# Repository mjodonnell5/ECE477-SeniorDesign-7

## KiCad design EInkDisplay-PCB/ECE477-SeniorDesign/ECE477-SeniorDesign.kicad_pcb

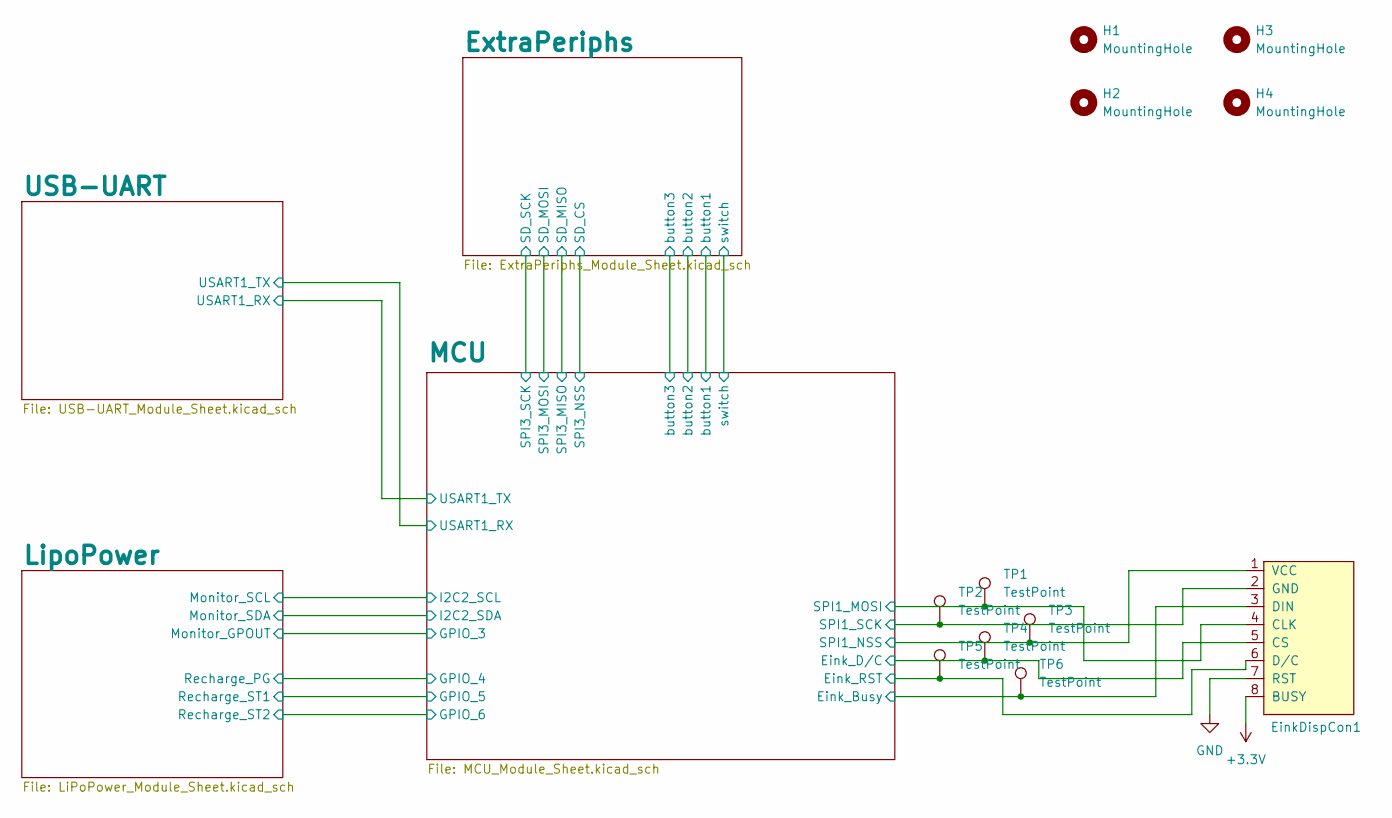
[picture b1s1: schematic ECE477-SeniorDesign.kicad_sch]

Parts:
EinkDispCon1: PinHeader_1x08_P2.54mm_Vertical
H1, H2, H3, H4: MountingHole; MountingHole_2.1mm
TP1, TP2, TP3, TP4, TP5, TP6: TestPoint; TestPoint_Pad_D2.0mm

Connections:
+3.3V: EinkDispCon1.8 (BUSY); also elsewhere on the board
/MCU/Eink_Busy: EinkDispCon1.3 (DIN), TP6.1; also elsewhere on the board
/MCU/Eink_D/C: EinkDispCon1.5 (CS), TP4.1; also elsewhere on the board
/MCU/Eink_RST: EinkDispCon1.6 (D/C), TP5.1; also elsewhere on the board
/MCU/SPI1_MOSI: EinkDispCon1.4 (CLK), TP1.1; also elsewhere on the board
/MCU/SPI1_NSS: EinkDispCon1.1 (VCC), TP3.1; also elsewhere on the board
/MCU/SPI1_SCK: EinkDispCon1.2 (GND), TP2.1; also elsewhere on the board
GND: EinkDispCon1.7 (RST); also elsewhere on the board

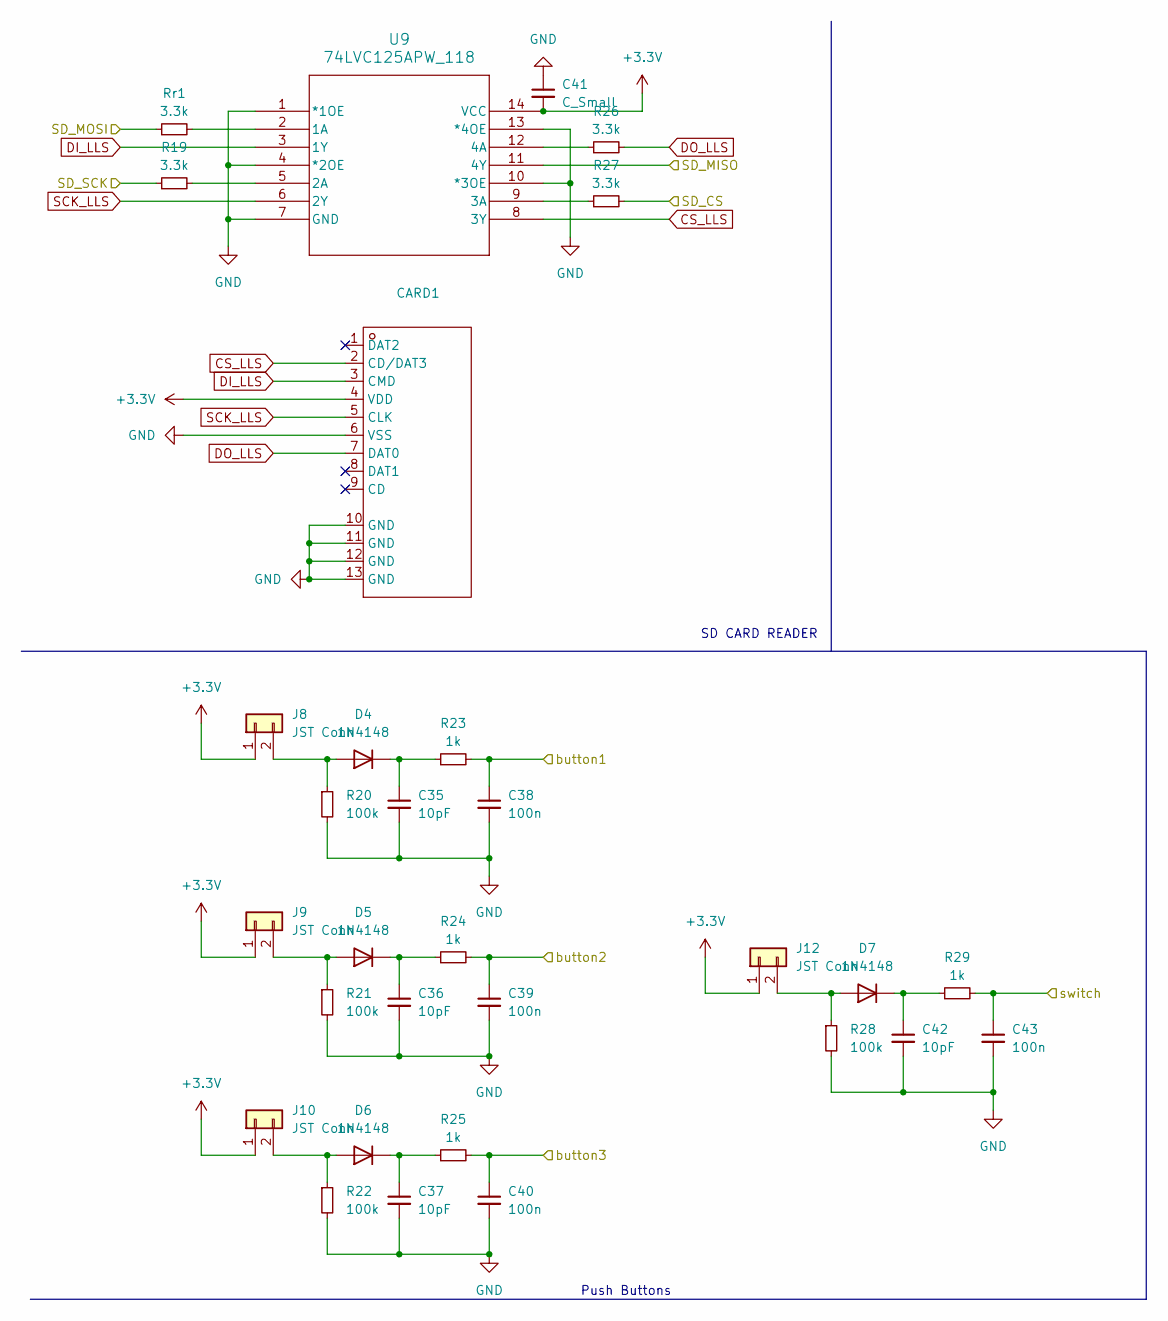
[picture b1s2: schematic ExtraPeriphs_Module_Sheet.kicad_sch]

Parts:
C35, C36, C37, C42: 10pF; C_0805_2012Metric_Pad1.18x1.45mm_HandSolder
C38, C39, C40, C43: 100n; C_0805_2012Metric_Pad1.18x1.45mm_HandSolder
C41: C_Small; C_0805_2012Metric_Pad1.18x1.45mm_HandSolder
CARD1: SD_reader_comp; Manufacturer Part XKTF-015-N; LCSC Part Name 自弹式 MicroSD卡(TF卡) 卡座
D4, D5, D6, D7: 1N4148; D_DO-35_SOD27_P7.62mm_Horizontal
J8, J9, J10, J12: JST Conn
R19, R26, R27: 3.3k; R_0805_2012Metric_Pad1.20x1.40mm_HandSolder
R20, R21, R22, R28: 100k; R_0805_2012Metric_Pad1.20x1.40mm_HandSolder
R23, R24, R25, R29: 1k; R_0805_2012Metric_Pad1.20x1.40mm_HandSolder
Rr1: 3.3k; R_0805_2012Metric_Pad1.20x1.40mm_HandSolder
U9: 74LVC125APW_118; 74LVC

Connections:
+3.3V: C41.2, CARD1.4 (VDD), J8.1, J9.1, J10.1, J12.1, U9.14 (VCC); also elsewhere on the board
/ExtraPeriphs/SD_CS: R27.2; also elsewhere on the board
/ExtraPeriphs/SD_MISO: U9.11 (4Y); also elsewhere on the board
/ExtraPeriphs/SD_MOSI: Rr1.1; also elsewhere on the board
/ExtraPeriphs/SD_SCK: R19.1; also elsewhere on the board
/ExtraPeriphs/button1: C38.1, R23.2; also elsewhere on the board
/ExtraPeriphs/button2: C39.1, R24.2; also elsewhere on the board
/ExtraPeriphs/button3: C40.1, R25.2; also elsewhere on the board
/ExtraPeriphs/switch: C43.1, R29.2; also elsewhere on the board
CS_LLS: CARD1.2 (CD/DAT3), U9.8 (3Y)
DI_LLS: CARD1.3 (CMD), U9.3 (1Y)
DO_LLS: CARD1.7 (DAT0), R26.2
GND: C35.2, C36.2, C37.2, C38.2, C39.2, C40.2, C41.1, C42.2, C43.2, CARD1.6 (VSS), CARD1.10 (GND), CARD1.11 (GND), CARD1.12 (GND), CARD1.13 (GND), R20.2, R21.2, R22.2, R28.2, U9.1 (*1OE), U9.4 (*2OE), U9.7 (GND), U9.10 (*3OE), U9.13 (*4OE); also elsewhere on the board
unnamed 44: D4.2 (A), J8.2, R20.1; also elsewhere on the board
unnamed: C35.1, D4.1 (K), R23.1
unnamed: D5.2 (A), J9.2, R21.1
unnamed: C36.1, D5.1 (K), R24.1
unnamed: D6.2 (A), J10.2, R22.1
unnamed: C37.1, D6.1 (K), R25.1
unnamed: D7.2 (A), J12.2, R28.1
unnamed: C42.1, D7.1 (K), R29.1
unnamed: Rr1.2, U9.2 (1A)
unnamed: R19.2, U9.5 (2A)
unnamed: R27.1, U9.9 (3A)
unnamed: R26.1, U9.12 (4A)
SCK_LLS: CARD1.5 (CLK), U9.6 (2Y)

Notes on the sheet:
SD CARD READER
Push Buttons

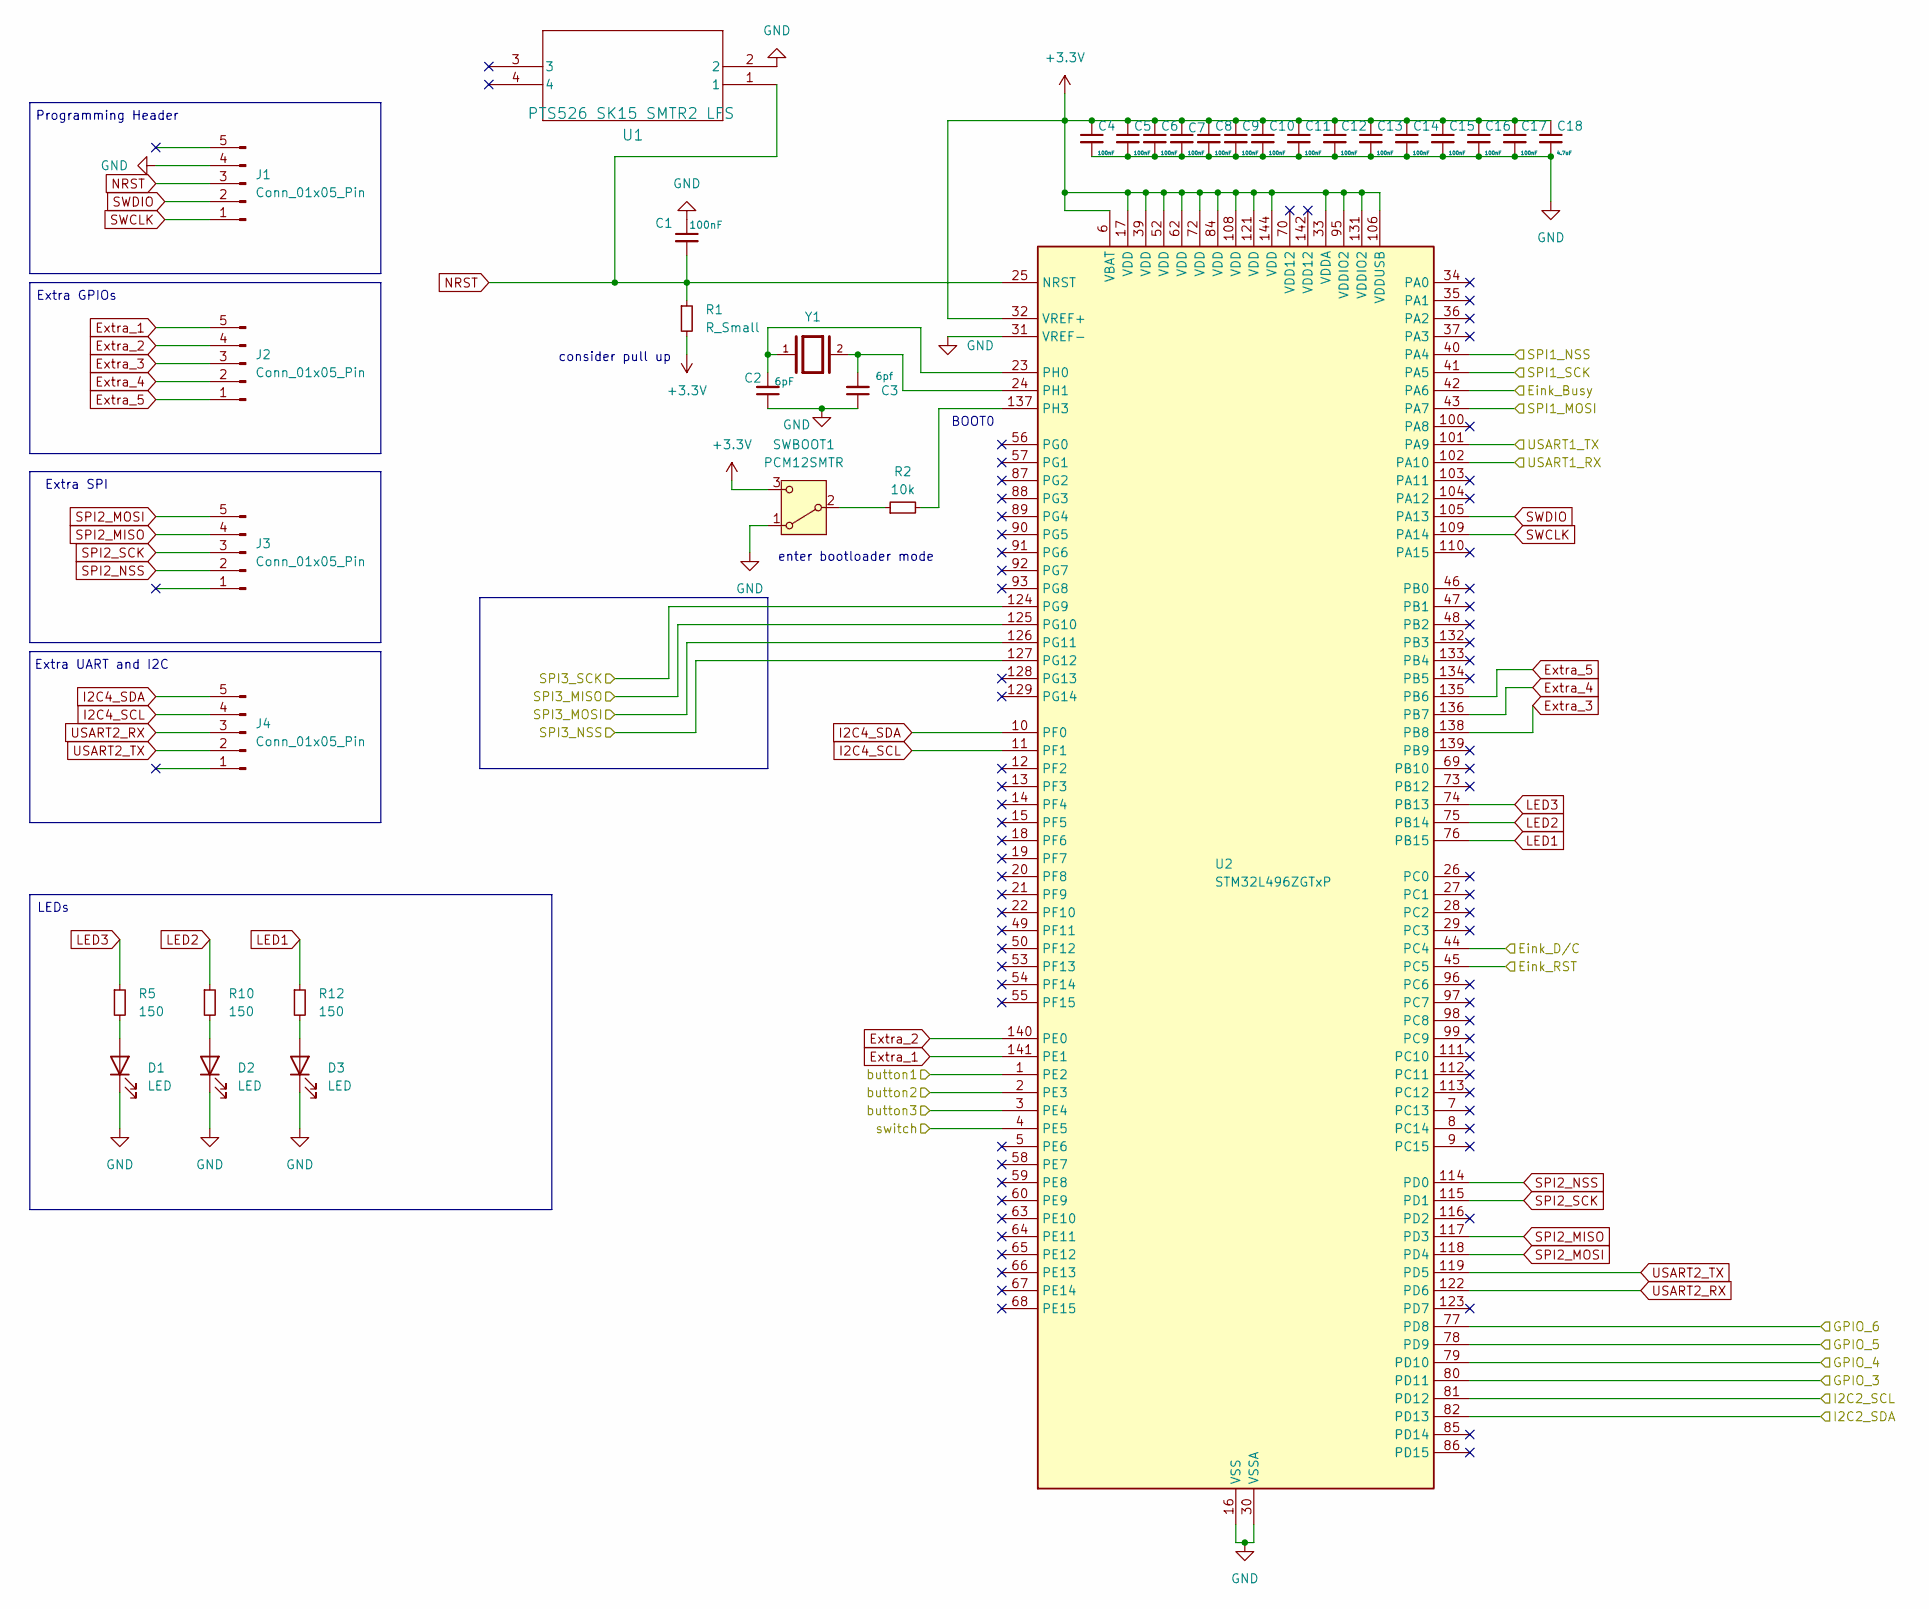
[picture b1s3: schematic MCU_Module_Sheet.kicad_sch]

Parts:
C1, C4, C5, C6, C7, C8, C9, C10, C11, C12, C13, C14, C15, C16, C17: 100nF; C_0805_2012Metric_Pad1.18x1.45mm_HandSolder
C2: 6pF; C_0805_2012Metric_Pad1.18x1.45mm_HandSolder
C3: 6pf; C_0805_2012Metric_Pad1.18x1.45mm_HandSolder
C18: 4.7uF; C_0805_2012Metric_Pad1.18x1.45mm_HandSolder
D1, D2, D3: LED; LED_0603_1608Metric
J1, J2, J3, J4: Conn_01x05_Pin; PinHeader_1x05_P2.54mm_Vertical
R1: R_Small; R_0805_2012Metric_Pad1.20x1.40mm_HandSolder
R2: 10k; R_0603_1608Metric_Pad0.98x0.95mm_HandSolder
R5, R10, R12: 150; R_0805_2012Metric_Pad1.20x1.40mm_HandSolder
SWBOOT1: PCM12SMTR; SW_SPDT_PCM12
U1: PTS526 SK15 SMTR2 LFS; PTS256
U2: STM32L496ZGTxP; LQFP-144_20x20mm_P0.5mm
Y1: CM9V-T1A-32.768KHZ-7PF-100PPM-TA-QC; PARTREV 8.0/10.2016

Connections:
+3.3V: C4.1, C5.1, C6.1, C7.1, C8.1, C9.1, C10.1, C11.1, C12.1, C13.1, C14.1, C15.1, C16.1, C17.1, C18.1, R1.2, SWBOOT1.3 (C), U2.6 (VBAT), U2.17 (VDD), U2.32 (VREF+), U2.33 (VDDA), U2.39 (VDD), U2.52 (VDD), U2.62 (VDD), U2.72 (VDD), U2.84 (VDD), U2.95 (VDDIO2), U2.106 (VDDUSB), U2.108 (VDD), U2.121 (VDD), U2.131 (VDDIO2), U2.144 (VDD); also elsewhere on the board
/ExtraPeriphs/SD_CS: U2.127 (PG12); also elsewhere on the board
/ExtraPeriphs/SD_MISO: U2.125 (PG10); also elsewhere on the board
/ExtraPeriphs/SD_MOSI: U2.126 (PG11); also elsewhere on the board
/ExtraPeriphs/SD_SCK: U2.124 (PG9); also elsewhere on the board
/ExtraPeriphs/button1: U2.1 (PE2); also elsewhere on the board
/ExtraPeriphs/button2: U2.2 (PE3); also elsewhere on the board
/ExtraPeriphs/button3: U2.3 (PE4); also elsewhere on the board
/ExtraPeriphs/switch: U2.4 (PE5); also elsewhere on the board
/LipoPower/Monitor_GPOUT: U2.80 (PD11); also elsewhere on the board
/LipoPower/Monitor_SCL: U2.81 (PD12); also elsewhere on the board
/LipoPower/Monitor_SDA: U2.82 (PD13); also elsewhere on the board
/LipoPower/Recharge_PG: U2.79 (PD10); also elsewhere on the board
/LipoPower/Recharge_ST1: U2.78 (PD9); also elsewhere on the board
/LipoPower/Recharge_ST2: U2.77 (PD8); also elsewhere on the board
/MCU/Eink_Busy: U2.42 (PA6); also elsewhere on the board
/MCU/Eink_D/C: U2.44 (PC4); also elsewhere on the board
/MCU/Eink_RST: U2.45 (PC5); also elsewhere on the board
/MCU/SPI1_MOSI: U2.43 (PA7); also elsewhere on the board
/MCU/SPI1_NSS: U2.40 (PA4); also elsewhere on the board
/MCU/SPI1_SCK: U2.41 (PA5); also elsewhere on the board
/MCU/USART1_RX: U2.102 (PA10); also elsewhere on the board
/MCU/USART1_TX: U2.101 (PA9); also elsewhere on the board
Extra_1: J2.5, U2.141 (PE1)
Extra_2: J2.4, U2.140 (PE0)
Extra_3: J2.3, U2.138 (PB8)
Extra_4: J2.2, U2.136 (PB7)
Extra_5: J2.1, U2.135 (PB6)
GND: C1.1, C2.1, C3.1, C4.2, C5.2, C6.2, C7.2, C8.2, C9.2, C10.2, C11.2, C12.2, C13.2, C14.2, C15.2, C16.2, C17.2, C18.2, D1.1 (K), D2.1 (K), D3.1 (K), J1.4, SWBOOT1.1 (A), U1.2, U2.16 (VSS), U2.30 (VSSA), U2.31 (VREF-), U2.38 (VSS), U2.51 (VSS), U2.61 (VSS), U2.71 (VSS), U2.83 (VSS), U2.94 (VSS), U2.107 (VSS), U2.120 (VSS), U2.130 (VSS), U2.143 (VSS); also elsewhere on the board
I2C4_SCL: J4.4, U2.11 (PF1)
I2C4_SDA: J4.5, U2.10 (PF0)
LED1: R12.1, U2.76 (PB15)
LED2: R10.1, U2.75 (PB14)
LED3: R5.1, U2.74 (PB13)
NRST: C1.2, J1.3, R1.1, U1.1, U2.25 (NRST)
unnamed: D1.2 (A), R5.2
unnamed: D2.2 (A), R10.2
unnamed: D3.2 (A), R12.2
unnamed: R2.1, SWBOOT1.2 (B)
unnamed: C2.2, U2.23 (PH0), Y1.1
unnamed: C3.2, U2.24 (PH1), Y1.2
unnamed: R2.2, U2.137 (PH3)
SPI2_MISO: J3.4, U2.117 (PD3)
SPI2_MOSI: J3.5, U2.118 (PD4)
SPI2_NSS: J3.2, U2.114 (PD0)
SPI2_SCK: J3.3, U2.115 (PD1)
SWCLK: J1.1, U2.109 (PA14)
SWDIO: J1.2, U2.105 (PA13)
USART2_RX: J4.3, U2.122 (PD6)
USART2_TX: J4.2, U2.119 (PD5)

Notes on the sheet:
consider pull up
BOOT0
Extra UART and I2C
Programming Header
enter bootloader mode
Extra SPI
Extra GPIOs
LEDs

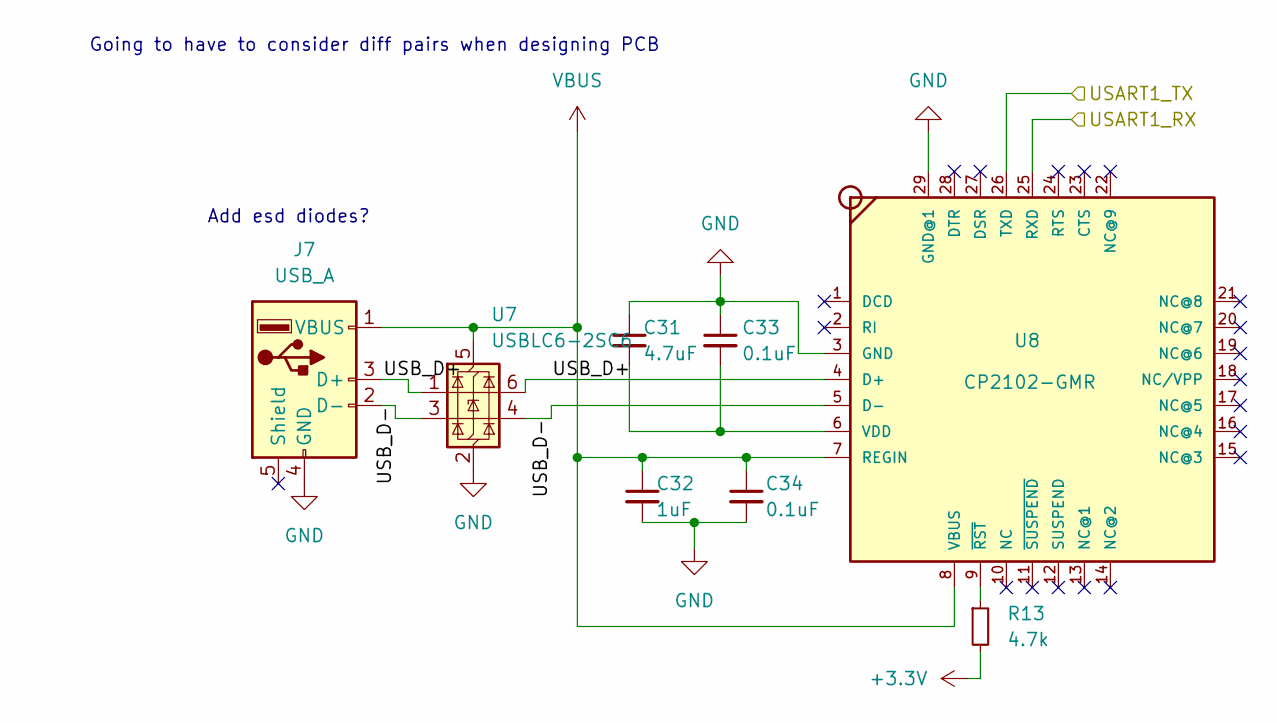
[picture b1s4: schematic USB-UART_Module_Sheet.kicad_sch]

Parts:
C31: 4.7uF; C_0805_2012Metric_Pad1.18x1.45mm_HandSolder
C32: 1uF; C_0805_2012Metric_Pad1.18x1.45mm_HandSolder
C33, C34: 0.1uF; C_0805_2012Metric_Pad1.18x1.45mm_HandSolder
J7: USB_A; USB_A_Receptacle_GCT_USB1046
R13: 4.7k; R_0805_2012Metric_Pad1.20x1.40mm_HandSolder
U7: USBLC6-2SC6; SOT-23-6
U8: CP2102-GMR; CP2102; MPN CP2102-GMR

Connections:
+3.3V: R13.2; also elsewhere on the board
/MCU/USART1_RX: U8.26 (TXD); also elsewhere on the board
/MCU/USART1_TX: U8.25 (RXD); also elsewhere on the board
/USB-UART/USB_D+: J7.3 (D+), U7.1 (I/O1), U7.6 (I/O1), U8.4 (D+)
/USB-UART/USB_D-: J7.2 (D-), U7.3 (I/O2), U7.4 (I/O2), U8.5 (D-)
GND: C31.1, C32.2, C33.1, C34.2, J7.4 (GND), J7.5 (Shield), U7.2 (GND), U8.3 (GND), U8.29 (GND@1); also elsewhere on the board
unnamed: C31.2, C33.2, U8.6 (VDD)
unnamed: R13.1, U8.9 (~RST)
VBUS: C32.1, C34.1, J7.1 (VBUS), U7.5 (VBUS), U8.7 (REGIN), U8.8 (VBUS); also elsewhere on the board

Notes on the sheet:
Add esd diodes?
Going to have to consider diff pairs when designing PCB

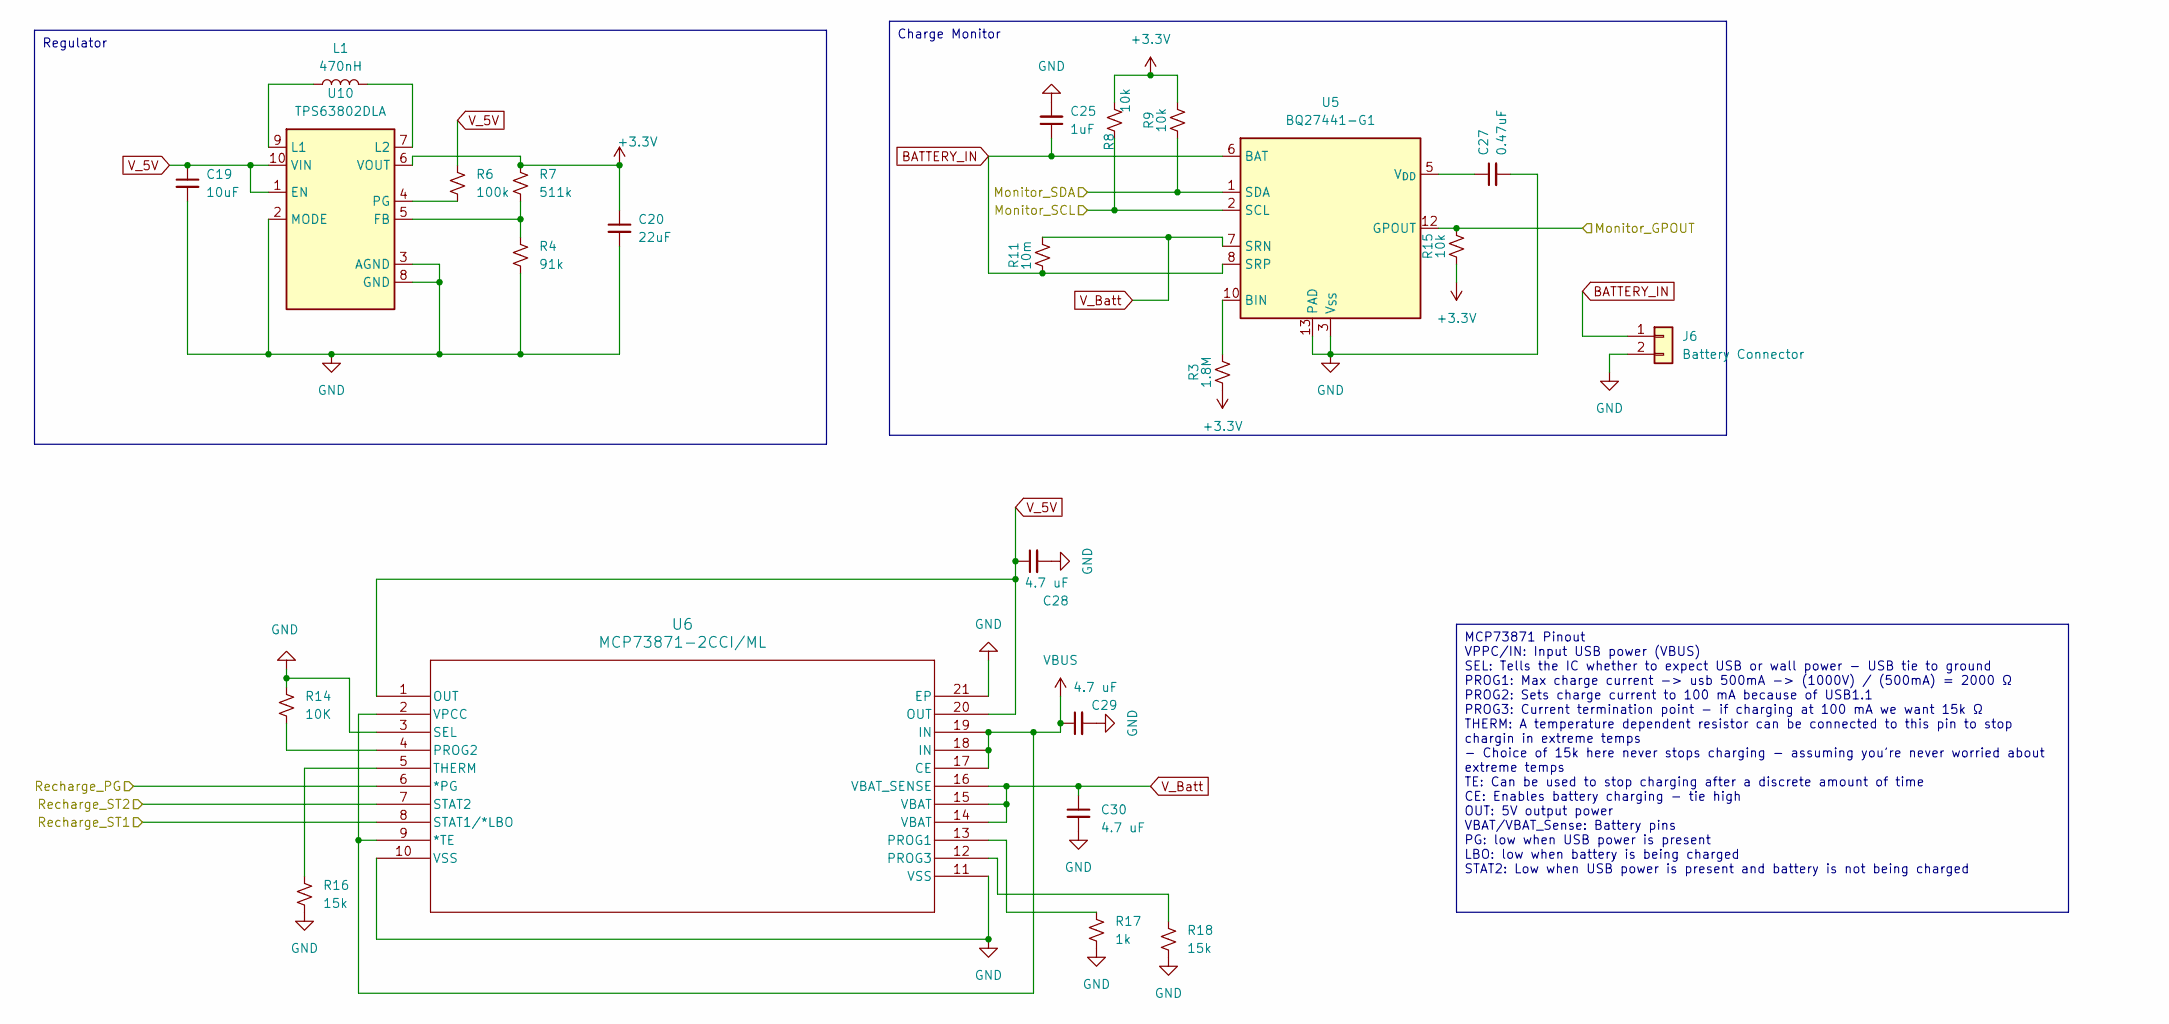
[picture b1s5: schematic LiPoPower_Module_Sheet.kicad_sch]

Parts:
C19: 10uF; C_0805_2012Metric_Pad1.18x1.45mm_HandSolder
C20: 22uF; C_0805_2012Metric_Pad1.18x1.45mm_HandSolder
C25: 1uF; C_0805_2012Metric_Pad1.18x1.45mm_HandSolder
C27: 0.47uF; C_0805_2012Metric_Pad1.18x1.45mm_HandSolder
C28, C29, C30: 4.7 uF; C_0805_2012Metric_Pad1.18x1.45mm_HandSolder
J6: Battery Connector; JST_PH_S2B-PH-SM4-TB_1x02-1MP_P2.00mm_Horizontal
L1: 470nH; IND_XFL4015_COC-L
R3: 1.8M; R_0805_2012Metric_Pad1.20x1.40mm_HandSolder
R4: 91k; R_0805_2012Metric_Pad1.20x1.40mm_HandSolder
R6: 100k; R_0805_2012Metric_Pad1.20x1.40mm_HandSolder
R7: 511k; R_0805_2012Metric_Pad1.20x1.40mm_HandSolder
R8, R9, R15: 10k; R_0805_2012Metric_Pad1.20x1.40mm_HandSolder
R11: 10m; R_0805_2012Metric_Pad1.20x1.40mm_HandSolder
R14: 10K; R_0805_2012Metric_Pad1.20x1.40mm_HandSolder
R16, R18: 15k; R_0805_2012Metric_Pad1.20x1.40mm_HandSolder
R17: 1k; R_0805_2012Metric_Pad1.20x1.40mm_HandSolder
U5: BQ27441-G1; Texas_S-PDSO-N12
U6: MCP73871-2CCI/ML; MCP73871; LCSC C5121473
U10: TPS63802DLA; TPS63802DLR; LCSC C2845237

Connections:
+3.3V: C20.1, R3.1, R7.1, R8.2, R9.2, R15.1, U10.6 (VOUT); also elsewhere on the board
/LipoPower/Monitor_GPOUT: R15.2, U5.12 (GPOUT); also elsewhere on the board
/LipoPower/Monitor_SCL: R8.1, U5.2 (SCL); also elsewhere on the board
/LipoPower/Monitor_SDA: R9.1, U5.1 (SDA); also elsewhere on the board
/LipoPower/Recharge_PG: U6.6 (*PG); also elsewhere on the board
/LipoPower/Recharge_ST1: U6.8 (STAT1/*LBO); also elsewhere on the board
/LipoPower/Recharge_ST2: U6.7 (STAT2); also elsewhere on the board
BATTERY_IN: C25.1, J6.1, R11.1, U5.6 (BAT), U5.8 (SRP)
GND: C19.2, C20.2, C25.2, C27.2, C28.2, C29.2, C30.2, J6.2, R4.2, R14.1, R16.1, R17.2, R18.1, U5.3 (V_{SS}), U5.13 (PAD), U6.3 (SEL), U6.10 (VSS), U6.11 (VSS), U6.21 (EP), U10.2 (MODE), U10.3 (AGND), U10.8 (GND); also elsewhere on the board
unnamed: R3.2, U5.10 (BIN)
unnamed: C27.1, U5.5 (V_{DD})
unnamed: R17.1, U6.13 (PROG1)
unnamed: R14.2, U6.4 (PROG2)
unnamed: R18.2, U6.12 (PROG3)
unnamed: R16.2, U6.5 (THERM)
unnamed: R4.1, R7.2, U10.5 (FB)
unnamed: L1.1, U10.9 (L1)
unnamed: L1.2, U10.7 (L2)
unnamed: R6.1, U10.4 (PG)
VBUS: C29.1, U6.2 (VPCC), U6.9 (*TE), U6.17 (CE), U6.18 (IN), U6.19 (IN); also elsewhere on the board
V_5V: C19.1, C28.1, R6.2, U6.1 (OUT), U6.20 (OUT), U10.1 (EN), U10.10 (VIN)
V_Batt: C30.1, R11.2, U5.7 (SRN), U6.14 (VBAT), U6.15 (VBAT), U6.16 (VBAT_SENSE)

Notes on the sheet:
Charge Monitor
MCP73871 Pinout VPPC/IN: Input USB power (VBUS) SEL: Tells the IC whether to expect USB or wall power - USB tie to ground PROG1: Max charge current -> usb 500mA -> (1000V) / (500mA) = 2000 Ω PROG2: Sets charge current to 100 mA because of USB1.1 PROG3: Current termination point - if charging at 100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
Regulator

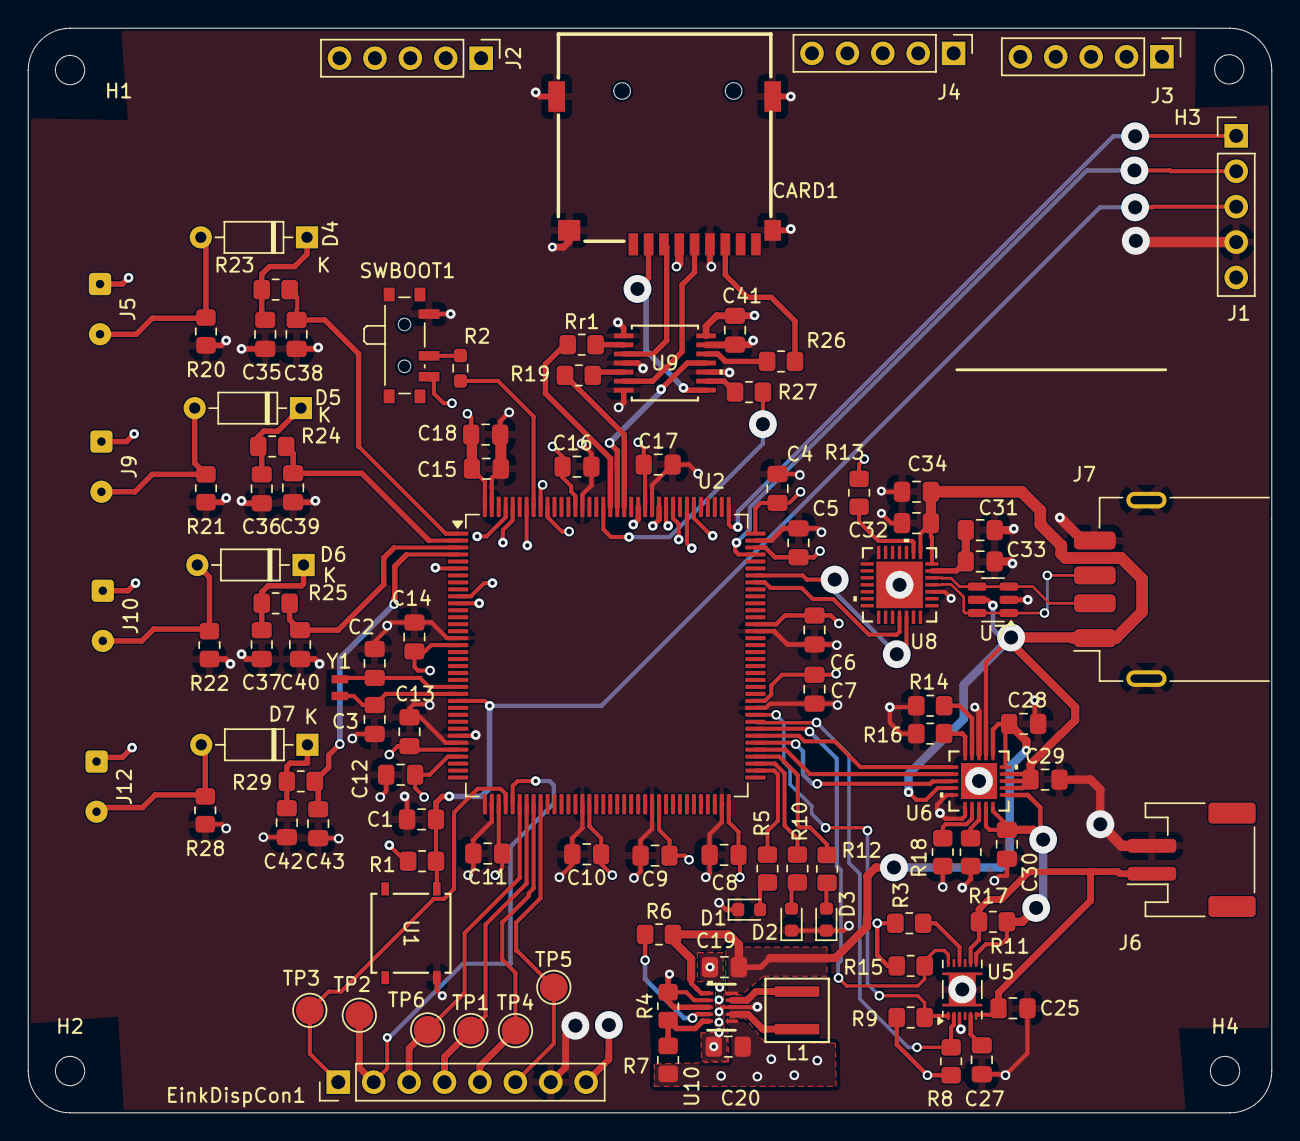
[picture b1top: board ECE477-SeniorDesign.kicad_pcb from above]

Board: 4 copper layers, 89.2 x 77.8 mm, 108 parts (0 on the bottom side), 84 nets.

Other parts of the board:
J5: Conn_01x02; SolderWire-0.1sqmm_1x02_P3.6mm_D0.4mm_OD1mm

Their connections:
+3.3V: J5.1; also elsewhere on the board
unnamed 44: J5.2; also elsewhere on the board

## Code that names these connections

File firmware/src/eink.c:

#include <stdint.h>
#include <stddef.h>
#include <string.h>
#include <stm32l496xx.h>

#include "../include/spi.h"
#include "../include/eink.h"
#include "../include/clock.h"
#include "../include/state.h"

uint8_t framebuffer[EINK_FRAMEBUFFER_SIZE] = {0xFF};
volatile uint8_t eink_busy = 0;

static void eink_send_cmd(uint8_t cmd)
{
    /* D/C low */
    GPIOC->BSRR = GPIO_BSRR_BR4;

    /* CS low */
    GPIOA->BSRR = GPIO_BSRR_BR4;

    spi_tx(EINK_SPI, cmd);

    /* CS high */
    GPIOA->BSRR = GPIO_BSRR_BS4;
}

static void eink_send_data(uint8_t data)
{
    /* D/C high */
    GPIOC->BSRR = GPIO_BSRR_BS4;

    /* CS low */
    GPIOA->BSRR = GPIO_BSRR_BR4;

    spi_tx(EINK_SPI, data);

    /* CS high */
    GPIOA->BSRR = GPIO_BSRR_BS4;
}

static void eink_pin_init()
{
    RCC->AHB2ENR |= RCC_AHB2ENR_GPIOAEN; //turn on A
    RCC->AHB2ENR |= RCC_AHB2ENR_GPIOCEN; //turn on C

    /* BUSY - PA6 (INPUT) ; RESET - PA9 ; D/C - PA8 */
    GPIOA->MODER &= ~(GPIO_MODER_MODER6 );
    RCC->APB2ENR |= RCC_APB2ENR_SYSCFGEN;
    SYSCFG->EXTICR[1] |= SYSCFG_EXTICR2_EXTI6_PA;
    EXTI->FTSR1 |= EXTI_FTSR1_FT6;
    EXTI->IMR1 |= EXTI_IMR1_IM6;

    NVIC->ISER[0] |= (1 << EXTI9_5_IRQn);
    // GPIOA->MODER |= (GPIO_MODER_MODER8_0 | GPIO_MODER_MODER9_0);

    /*; RESET - PC5 ; D/C - PC4 */
    GPIOC->MODER &= ~(GPIO_MODER_MODER4 | GPIO_MODER_MODER5);
    GPIOC->MODER |= (GPIO_MODER_MODER4_0 | GPIO_MODER_MODER5_0);

    /* High speed ...might need these?*/
    // GPIOA->OSPEEDR &= ~(GPIO_OSPEEDR_OSPEED6 | GPIO_OSPEEDR_OSPEED8 | GPIO_OSPEEDR_OSPEED9);
    // GPIOA->OSPEEDR |= GPIO_OSPEEDR_OSPEED6_1 | GPIO_OSPEEDR_OSPEED8_1 | GPIO_OSPEEDR_OSPEED9_1;

}


void eink_wait_until_idle()
{
    /* The all mightly magical command */
    // eink_send_cmd(0x71);

    // while((GPIOA->IDR & GPIO_IDR_ID6) == 1) {
    //     eink_send_cmd(0x71);
    // }
    while (eink_busy == 1) {};

    // delay_ms(100);
}

static void eink_reset()
{
    /* Set RESET high */
    GPIOC->BSRR = GPIO_BSRR_BS5;
    delay_ms(100);

    /* RESET is active low */
    GPIOC->BSRR = GPIO_BSRR_BR5;

    delay_ms(2);

    /* Set RESET high */
    GPIOC->BSRR = GPIO_BSRR_BS5;

    delay_ms(100);
}

void eink_init()
{
    eink_pin_init();

    eink_reset();
    eink_send_cmd(0x12);
    eink_wait_until_idle();
    delay_ms(100);

    delay_ms(10);

    eink_send_cmd(0x21);
    eink_send_data(0x40);
    eink_send_data(0x00);

    eink_send_cmd(0x3C);
    eink_send_data(0x05);

    /* Stuff for FAST MODE */
    eink_send_cmd(0x1A);
    eink_send_data(0x5A);
    eink_send_cmd(0x22);
    eink_send_data(0x91);
    eink_send_cmd(0x20);
    eink_wait_until_idle();
    delay_ms(100);

    eink_send_cmd(0x11);
    if (left_handed) {
        eink_send_data(0x03);
    } else {
        eink_send_data(0x00);
    }

    eink_send_cmd(0x44); 
    if (left_handed) {
        eink_send_data(0x00);
        eink_send_data(0x31); 
    } else {
        eink_send_data(0x31); 
        eink_send_data(0x00);
    }
    
    eink_send_cmd(0x45);
    if (left_handed) {
        eink_send_data(0x00);
        eink_send_data(0x00);  
        eink_send_data(0x2B);
        eink_send_data(0x01);
    } else {
        eink_send_data(0x2B);
        eink_send_data(0x01);
        eink_send_data(0x00);
        eink_send_data(0x00);  
    }

    if (left_handed) {
        eink_send_cmd(0x4E); 
        eink_send_data(0x00);

        eink_send_cmd(0x4F); 
        eink_send_data(0x00);
        eink_send_data(0x00);  
    } else {
        eink_send_cmd(0x4E); 
        eink_send_data(0x31);

        eink_send_cmd(0x4F); 
        eink_send_data(0x2B);
        eink_send_data(0x01);  
    }
    eink_wait_until_idle();
    // delay_ms(100);
}

inline void eink_draw_pixel(uint16_t x, uint16_t y, uint8_t col)
{
    uint32_t index = y * EINK_WIDTH + x;
    uint16_t byte_index = index / 8;

    if (x >= EINK_WIDTH || y >= EINK_HEIGHT) return;

    if (col == WHITE) {
        framebuffer[byte_index] |= (0x80 >> (x % 8));
    } else {
        framebuffer[byte_index] &= ~(0x80 >> (x % 8));
    }
}

static void eink_turn_on_display()
{
    /* FAST MODE */
    eink_send_cmd(0x22);
    eink_send_data(0xC7);
    eink_send_cmd(0x20);
    eink_wait_until_idle();
}

void eink_render_framebuffer()
{
    eink_busy = 1;
    /* Start writing into B/W ram */
    eink_send_cmd(0x24);

    for (uint16_t i = 0; i < EINK_FRAMEBUFFER_SIZE; ++i) {
        eink_send_data(framebuffer[i]);
    }

    eink_turn_on_display();
}

void eink_clear(uint8_t col)
{
    memset(framebuffer, col, EINK_FRAMEBUFFER_SIZE);
}

void eink_sleep()
{
    eink_send_cmd(0x10);
    eink_send_data(0x01);
    delay_ms(100);
}

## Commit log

2025-01-16 Add Blocks
    Adding USB-UART block
2025-01-28 Pushing some basic SPI stuff, init is not setup for epaper at the moment and is just copied from 362
2025-01-28 I think SPI config for eink should be good
2025-01-28 Accidently pushed the default READMEs and a personal config file
2025-01-28 Starting to setup eink init based on data sheet, I will go through and see what we need to modify once I copy it all from the data sheet
2025-01-28 Edits
2025-01-28 switching over to V2
2025-01-28 Adding Power Sheet
2025-01-28 Adding Component Library
    -named einkcomponent library
2025-01-28 Trying to add some drawing functions and rendering the framebuffer
2025-01-30 USB Complete
2025-01-30 Pushing because its broken :(
2025-01-30 Lot of changes
2025-02-02 push
2025-02-03 Still scrambled
2025-02-04 Adding SD
2025-02-04 fixing
2025-02-04 It works, thanks Zoe
2025-02-04 Fixing SD w SPI
2025-02-05 Cleaning stuff up and optimizing a bit
2025-02-05 IT WORKS
2025-02-06 eink stuff should be done
2025-02-12 introducing power sch
2025-02-12 fixing things
2025-02-12 should have pushed before, also this is not based on main so hopefully no merge conflicts
2025-02-13 adding my sd card code ALLL
2025-02-14 0805
2025-02-15 Testing wrapping of strings and displaying flashcards
2025-02-15 I forget
2025-02-18 Testing adding flashcard front/backs
2025-02-18 adding skeleton functions until SD stuff is done
2025-02-19 Update USB-UART_Module_Sheet.kicad_sch
    Add ESD diode
2025-02-19 Update ECE477-SeniorDesign.kicad_pcb
    All UART / Voltage reg components
2025-02-19 change
2025-02-19 Pushing
2025-02-19 adding UART files
2025-02-19 SD_Reader Footprint
2025-02-20 Starting to clean up, I really should make a new branch though lol
2025-02-20 Lotta changes
2025-02-20 added parseJSON_file and changed main
2025-02-20 Did a decent amount of cleanup and moved buttons so Zoe and I can integrate
2025-02-21 Clock stuff, not finished
2025-02-21 Scrolling, clock, delaying, all kinds of fun stuff. This PR is WAY too big lol
2025-02-21 fixed pinout
2025-02-21 new sd card name
2025-02-21 Moving stuff to firmware
2025-02-21 RAAAAAAAAAAAAAAAAA
2025-02-22 centered!
2025-02-22 Prepping for download
2025-02-23 onto PCB
2025-02-23 SD card updates
2025-02-23 power & power pcb layout
2025-02-24 Setting up download flashcards
2025-02-25 Correcting
2025-02-25 Ensuring file save
2025-02-25 layout and coulomb counter sch update
2025-02-26 pcb update
2025-02-27 whole lotta changes
2025-02-27 We can get files over UART
2025-02-27 Layout update
2025-02-28 Fixed clock frequency, centered string wrapping and did some cleaning up
2025-02-28 Can now receive again with clock updates
2025-03-02 Added bounds checking and better headers
2025-03-03 Power Routing
2025-03-03 adding application v1 and v2
2025-03-03 finished cleanup
2025-03-03 again
2025-03-04 pusj
2025-03-04 done
2025-03-05 I implemented font stuff but am not in lab to test
2025-03-06 pusbh
2025-03-06 Variable fonts work!
2025-03-06 Regulator footprint and sch update
2025-03-07 app v3 added
2025-03-11 Sch update
2025-03-12 Setup basic stuff to get it ready
2025-03-12 changes to new app
2025-03-12 LONG PRESSING WORKS
2025-03-13 rev 2
2025-03-13 rev3
2025-03-13 new commands
2025-03-13 add set name
2025-03-13 implementing state logic in regards to the long button press
2025-03-13 I am dumb and not pending the render and I had the state machine messed up, it was running too fast, need delay or to WFI
2025-03-26 size restriction
2025-03-26 not working now?
2025-03-27 Refactor button and state machine stuff
2025-03-31 This branch is just random stuff at this point, added delete confirmation and am starting to add settings
2025-04-01 newest app
2025-04-01 adding battery code
2025-04-01 Forgot to actually implement the shuffling
2025-04-02 battery changes
2025-04-02 new pins
2025-04-02 all added - cole check
2025-04-03 Power stuff should work, just haven't set up power switch pinout stuff
2025-04-03 Starting to disable stuff
2025-04-03 centering
2025-04-04 scroll but glitchy!
2025-04-07 newest changes
2025-04-07 new pins uart
2025-04-08 Lotta UI changes
2025-04-09 fixing appv3 on this branch
2025-04-09 app has new format
2025-04-09 Forgot to push yesterday
2025-04-10 changes to the firmware side
2025-04-10 sike using a struct
2025-04-10 build error fix
2025-04-10 RTC seems to work
2025-04-10 rtc stuff and setting up sd card reader
2025-04-11 new battery pins
2025-04-13 I forget lol
2025-04-13 Readding writing to the SD when downloading
2025-04-14 tested num cards, works!
2025-04-14 adding long filenames
2025-04-17 Gotta switch back
2025-04-17 Variable fonts, can choose dominant hand, button hints
2025-04-17 good app!
2025-04-17 metadata stuff added but not tested
2025-04-17 Fixed button hints for right handed mode
2025-04-18 Eink busy works properly :)
2025-04-20 Rewrite complete, haven't tested anything except home nav yet
2025-04-20 starting to think aobut coalescing
2025-04-20 coalescing works!
2025-04-20 Busy isn't going low after writing sleep image?
2025-04-22 No more NULL function ptrs
2025-04-25 it all works! didin't fully clean up ui drawing code though
2025-04-28 metadata changes
2025-05-01 PLS WORK FOR SPARK PLEASEEEEEEEEEEE
